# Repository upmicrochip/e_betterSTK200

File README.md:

# Better STK200 - AVR programmer.

## EAGLE 7.1.0 files formats:
1. *.sch - EAGLE schematic
2. *.brd - EAGLE PCB board

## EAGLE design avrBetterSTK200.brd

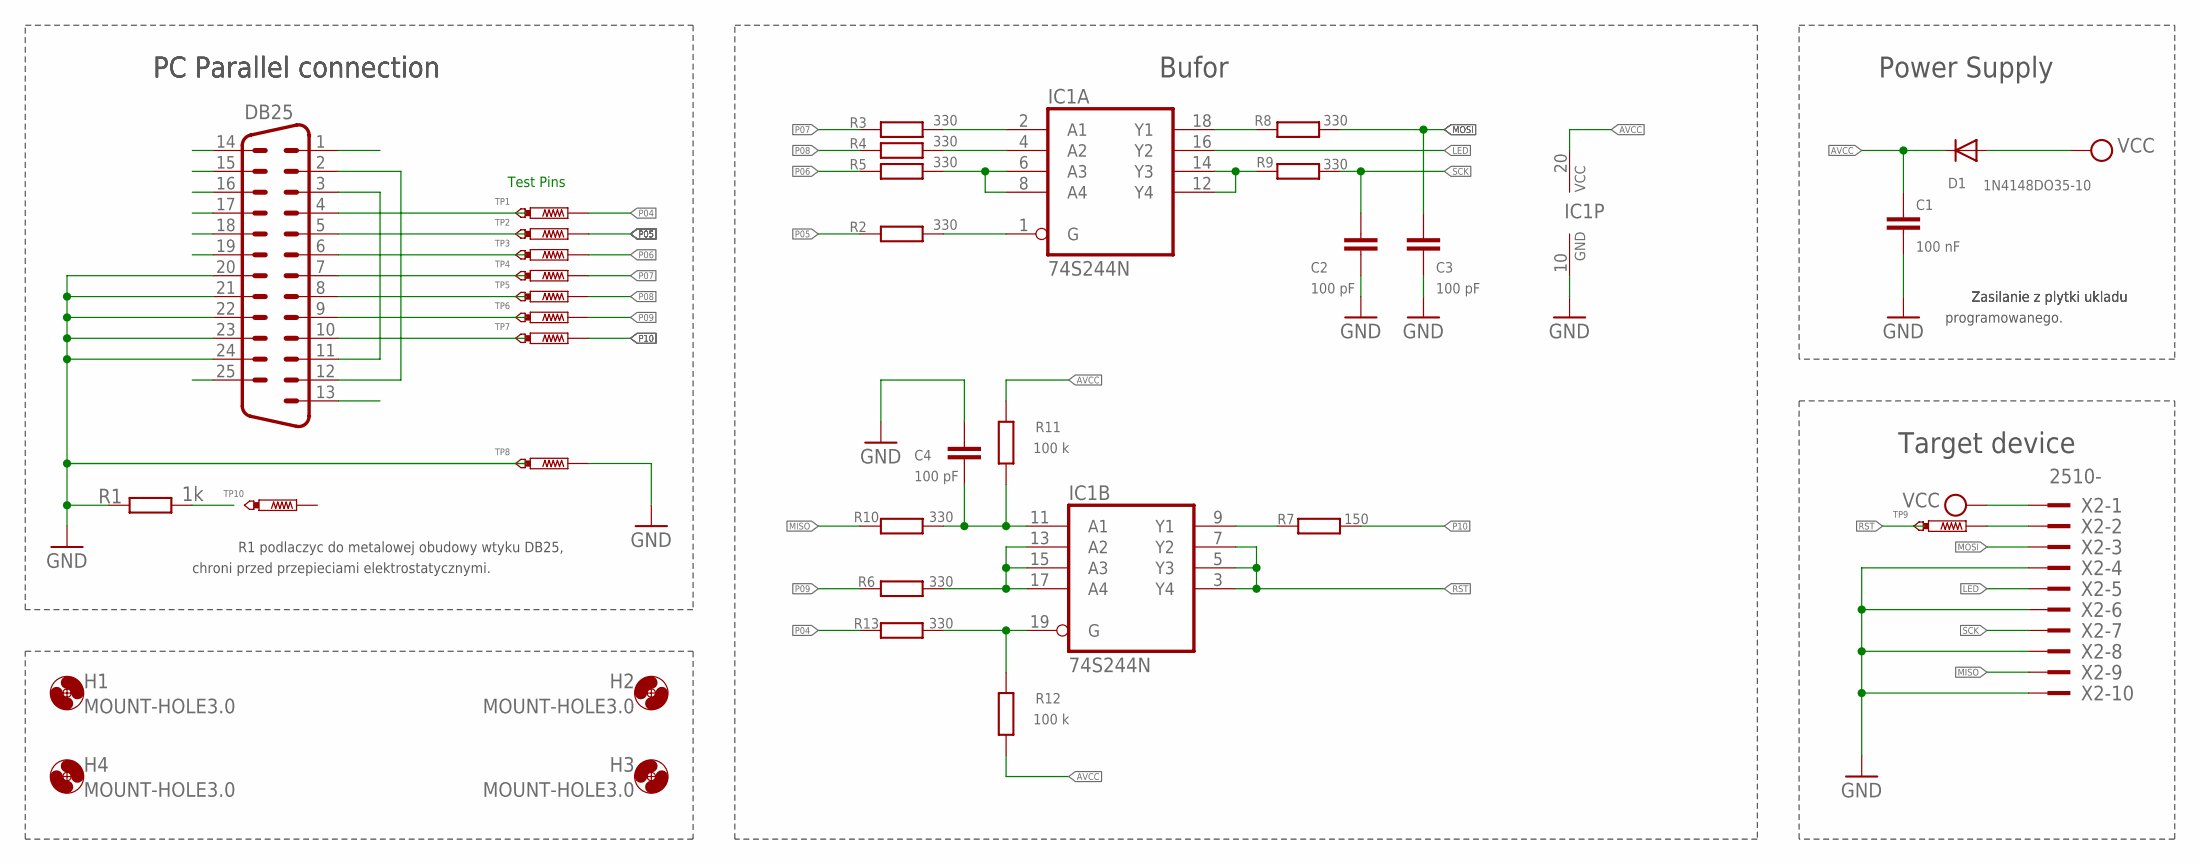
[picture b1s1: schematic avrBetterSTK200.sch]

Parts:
C1: 100 nF; C050-035X075
C2, C3, C4: 100 pF; C050-035X075
D1: 1N4148DO35-10; DO35-10
DB25: M25V
H1, H2, H3, H4: MOUNT-HOLE3.0; 3,0
IC1: 74S244N; DIL20
R1: 1k; 0207/10
R2, R3, R4, R5, R6, R8, R9, R10, R13: 330; 0207/10
R7: 150; 0207/10
R11, R12: 100 k; 0207/10
TP1, TP2, TP3, TP4, TP5, TP6, TP7, TP8, TP9, TP10: PTR1PAD1-17Y; P1-17Y
X2: 2510-; PAK100/2500-10

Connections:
AVCC: C1.1, D1.C, IC1.20 (VCC), R11.2, R12.1
GND: C1.2, C2.2, C3.2, C4.1, DB25.20, DB25.21, DB25.22, DB25.23, DB25.24, IC1.10 (GND), R1.1, TP8.TP, X2.4, X2.6, X2.8, X2.10
LED: IC1.16 (Y2), X2.5
MISO: R10.1, X2.9
MOSI: C3.1, R8.2, X2.3
unnamed: DB25.2, DB25.12
unnamed: DB25.3, DB25.11
unnamed: IC1.1 (G), R2.2
unnamed: IC1.6 (A3), IC1.8 (A4), R5.2
unnamed: IC1.4 (A2), R4.2
unnamed: IC1.2 (A1), R3.2
unnamed: IC1.9 (Y1), R7.1
unnamed: IC1.13 (A2), IC1.15 (A3), IC1.17 (A4), R6.2
unnamed: IC1.18 (Y1), R8.1
unnamed: IC1.12 (Y4), IC1.14 (Y3), R9.1
unnamed: C4.2, IC1.11 (A1), R10.2, R11.1
unnamed: IC1.19 (G), R12.2, R13.2
P04: R13.1, TP1.TP
P05: R2.1, TP2.TP
P06: R5.1, TP3.TP
P07: R3.1, TP4.TP
P08: R4.1, TP5.TP
P09: R6.1, TP6.TP
P10: R7.2, TP7.TP
PAD1: DB25.14
PAD2: DB25.15
PAD3: DB25.16
PAD4: DB25.17
PAD5: DB25.18
PAD6: DB25.19
PAD7: DB25.25
PAD8: DB25.1
PAD9: DB25.13
RST: IC1.3 (Y4), IC1.5 (Y3), IC1.7 (Y2), TP9.TP, X2.2
SCK: C2.1, R9.2, X2.7
TP1: DB25.4
TP2: DB25.5
TP3: DB25.6
TP4: DB25.7
TP5: DB25.8
TP6: DB25.9
TP7: DB25.10
TP10: R1.2
VCC: D1.A, X2.1

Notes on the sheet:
Test Pins
PC Parallel connection
chroni przed przepieciami elektrostatycznymi.
Power Supply
R1 podlaczyc do metalowej obudowy wtyku DB25,
Zasilanie z plytki ukladu
programowanego.
Target device
Bufor

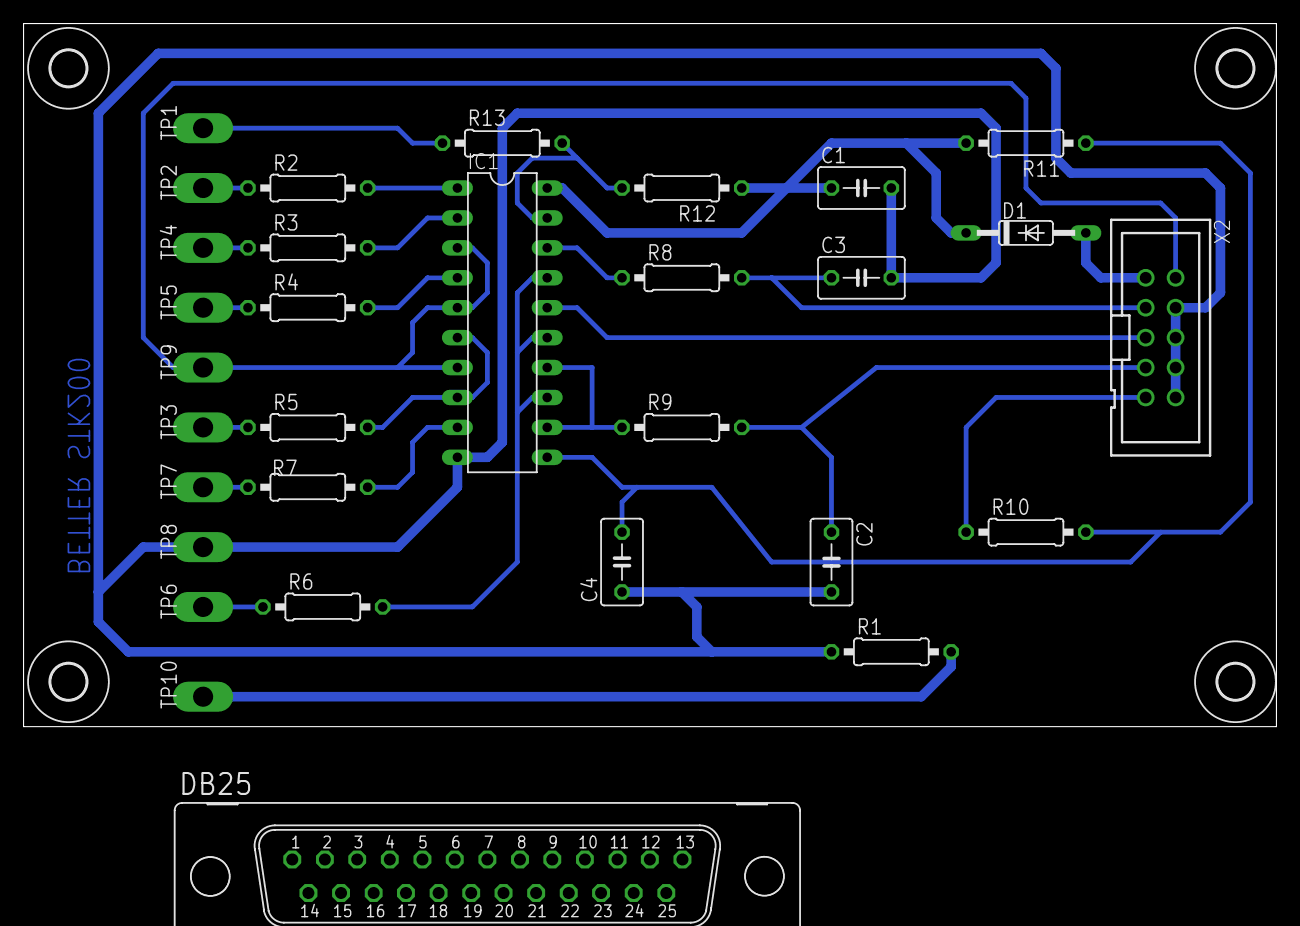
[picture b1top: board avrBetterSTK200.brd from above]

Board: 2 copper layers, 106.3 x 59.7 mm, 35 parts (0 on the bottom side), 27 nets.
